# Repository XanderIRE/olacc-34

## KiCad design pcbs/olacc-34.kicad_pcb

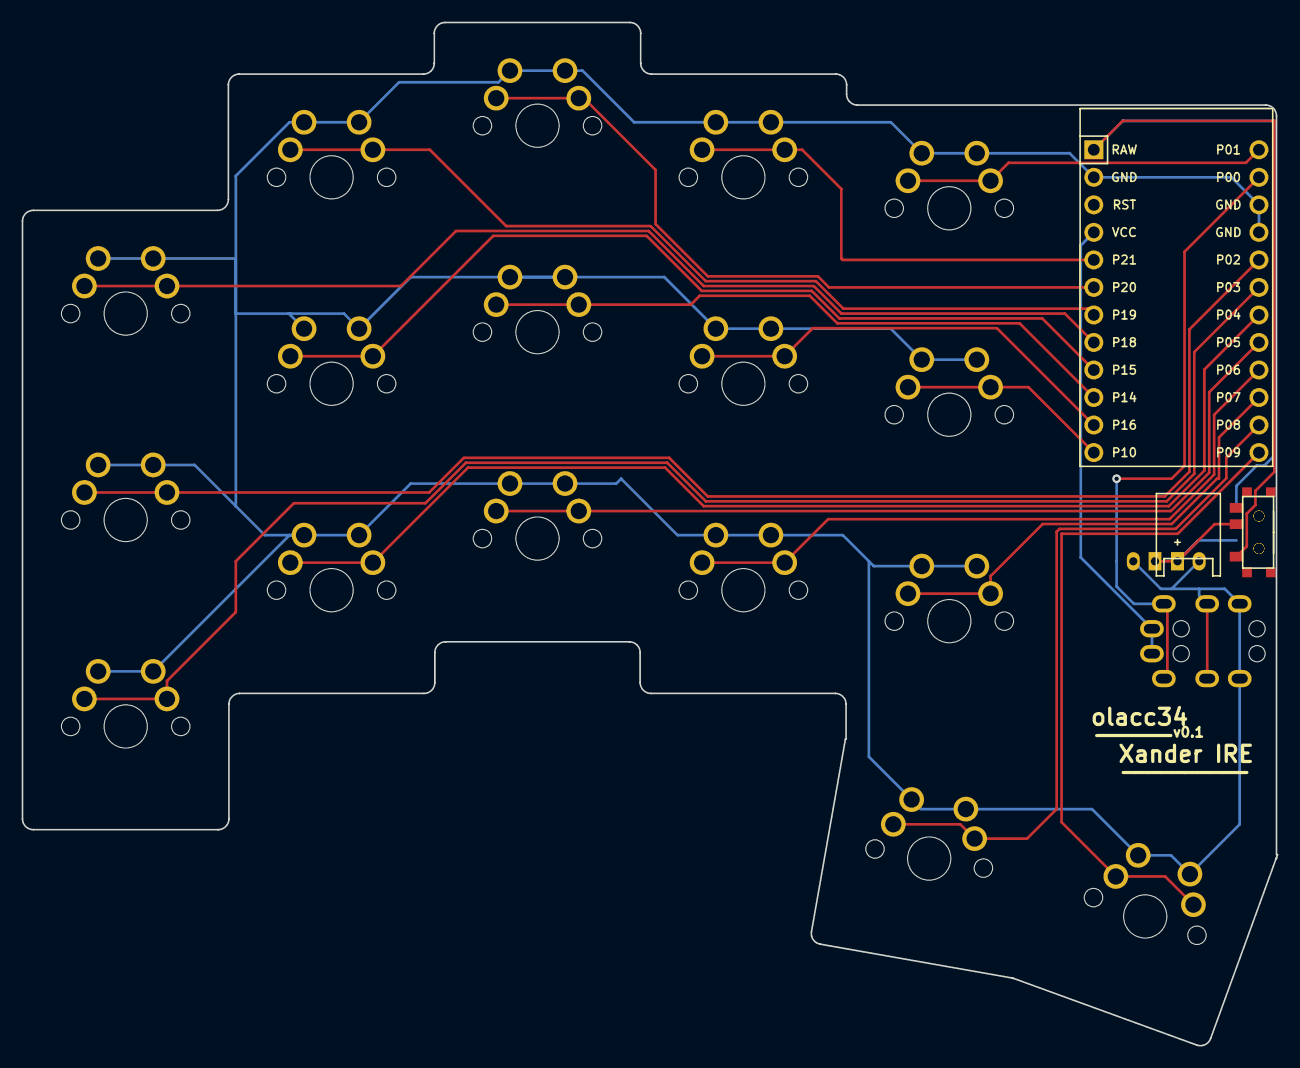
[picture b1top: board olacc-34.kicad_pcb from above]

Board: 2 copper layers, 115.8 x 94.4 mm, 23 parts (1 on the bottom side), 22 nets.

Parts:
JST1, JST1#2: JST_PH_S2B-PH-K_02x2.00mm_Angled
MCU1: ProMicro
S1, S2, S3, S4, S5, S6, S7, S8, S9, S10, S11, S12, S13, S14, S15, S16, S17: MX
T1, T2: SPDT_C128955
TRRS1: TRRS-PJ-320A-dual

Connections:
BAT: JST1.1, JST1#2.1, T1.2, T2.2
GND: JST1.2, JST1#2.2, MCU1.2, MCU1.15, MCU1.16, S1.1, S2.1, S3.1, S4.1, S5.1, S6.1, S7.1, S8.1, S9.1, S10.1, S11.1, S12.1, S13.1, S14.1, S15.1, S16.1, S17.1, TRRS1.3, TRRS1.4
P0: MCU1.14, TRRS1.2
RAW: MCU1.1, T1.1, T2.1
VCC: MCU1.4, TRRS1.1
matrix_index_bottom: MCU1.21, S10.2
matrix_index_home: MCU1.11, S11.2
matrix_index_top: MCU1.5, S12.2
matrix_inner_bottom: MCU1.22, S13.2
matrix_inner_home: MCU1.12, S14.2
matrix_inner_top: MCU1.13, S15.2
matrix_middle_bottom: MCU1.20, S7.2
matrix_middle_home: MCU1.10, S8.2
matrix_middle_top: MCU1.6, S9.2
matrix_pinky_bottom: MCU1.18, S1.2
matrix_pinky_home: MCU1.17, S2.2
matrix_pinky_top: MCU1.8, S3.2
matrix_ring_bottom: MCU1.19, S4.2
matrix_ring_home: MCU1.9, S5.2
matrix_ring_top: MCU1.7, S6.2
thumb_reachy: MCU1.24, S17.2
thumb_tucky: MCU1.23, S16.2

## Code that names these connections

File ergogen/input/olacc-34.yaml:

points:
  zones:
    matrix:
      columns:
        pinky:
        ring.key.stagger: 0.66U
        middle.key.stagger: 0.25U
        index.key.stagger: -0.25U
        inner.key.stagger: -0.15U
      rows:
        bottom.padding: U
        home.padding: U
        top.padding: U
    thumb:
      anchor:
        ref: matrix_index_bottom
        shift: [0.9U, -1.3U]
        rotate: -10
      columns:
        tucky:
          key.name: thumb_tucky
        reachy:
          key.spread: U
          key.splay: -10
          key.origin: [-0.5U, -0.5U]
          key.name: thumb_reachy

outlines:
  raw:
# Outline of keys and micro controller area
    - what: rectangle
      where: true
      asym: left
      size: [1U,1U]
      corner:
    - what: rectangle
      where: thumb_reachy
      size: [1.17U, 3U]
      adjust:
        ref: matrix_inner_home
        shift: [1U, 0]
    - what: rectangle
      where: thumb_reachy
      size: [1.17U, 2.3U]
      adjust:
        ref: matrix_inner_bottom
        shift: [1U, 0]
    - what: rectangle
      where: matrix_inner_bottom
      size: [1U, 2U]
    - what: rectangle
      where: thumb_tucky
      size: [1U, 1U]
    - what: rectangle
      where: thumb_reachy
      size: [1U, 1U]
      adjust:
          ref: thumb_reachy
          rotate: 0
          shift: [-5, 0]

# # Padding out bottom of board
#     - what: rectangle
#       where: thumb_tucky
#       size: [3U, 1.1U]
#       adjust: 
#         ref: thumb_tucky
#         shift: [-2U, 1]
#     - what: rectangle
#       where: matrix_pinky_bottom
#       size: [U, 2U]
#       adjust:
#         ref: matrix_middle_bottom
#         shift: [-2U, -8.3]
#     - what: rectangle
#       where: matrix_middle_bottom
#       size: [3U, 2U]

  panel:
    - what: outline
      name: raw
      fillet: 1
  switch_cutouts:
    - what: rectangle
      where: true
      asym: left
      size: 14
      bound: false
  switch_plate:
    main:
      what: outline
      name: panel
      fillet: 0.5
    keyholes:
      what: outline
      name: switch_cutouts
      operation: subtract
  preview:
    [panel]

pcbs:
  olacc-34:
    outlines:
      board:
        outline: preview
      keycaps:
        outline: switch_cutouts
        layer: Eco1.User
    footprints:
      mx_solder:
        what: mx
        where: true
        params:
          from: GND
          to: "{{name}}"
          reverse: true
          keycaps: true
      # mx_hotswap:
      #   what: mx
      #   where: true
      #   adjust:
      #     rotate: 180
      #   params:
      #     from: GND
      #     to: "{{name}}"
      #     reverse: true
      #     keycaps: true
      #     hotswap: true
      mcu:
        what: promicro
        where:
          - ref: matrix_inner_home
            shift: [1.1U, 0.55U]
            rotate: -90
        params:
          P2: matrix_pinky_home
          P18: matrix_pinky_top
          P19: matrix_ring_top
          P20: matrix_middle_top
          P21: matrix_index_top
          P15: matrix_ring_home
          P14: matrix_middle_home
          P16: matrix_index_home
          P10: matrix_inner_home
          P1: matrix_inner_top
          P7: matrix_inner_bottom
          P3: matrix_pinky_bottom
          P4: matrix_ring_bottom
          P5: matrix_middle_bottom
          P6: matrix_index_bottom
          P8: thumb_tucky
          P9: thumb_reachy
      powerswitch_front:
        what: slider
        where:
          ref: matrix_inner_bottom
          rotate: -90
          shift: [1.5U, 8.2]
        params:
          from: RAW
          to: BAT
          side: F
      powerswitch_back:
        what: slider
        where:
          ref: matrix_inner_bottom
          rotate: -90
          shift: [1.5U, 8.2]
        params:
          from: RAW
          to: BAT
          side: B
      jstph:
        what: jstph
        where:
          ref: matrix_inner_bottom
          shift: [1U, 0.3U]
          rotate: 180
        params:
          pos: BAT
          neg: GND
          side: B
      trrs:
        what: trrs
        where:
          ref: matrix_inner_bottom
          shift: [30, -3]
          rotate: -90
        params:
          mirror: true
          reverse: true
          symmetric: false
          A: GND
          B: GND
          C: P0
          D: VCC

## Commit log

2023-03-26 add ergogen yaml file
2023-03-26 add generated keyboard files
2023-03-27 add pinout connection to TRRS jack
2023-03-27 correct serial pin conn for trrs
2023-03-27 add qmk keyboard files
2023-03-27 add keymaps with updated controls
2023-03-27 add hex files for flashing keymap
2023-03-27 update serial pin out trrs
2023-03-27 update pcbs with trrs and bat conns
2023-03-27 update gerber with trrs and bat
2023-03-29 update custom keymap thumb keys
2023-03-29 Fix reversed pins for right half
